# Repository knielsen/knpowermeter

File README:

Tiva TM4C version of blipduino.

Read blips on a powermeter with a photo-diode.
Use ADC comparator to detect blips.
Send data to master node using nRF24L01+.

Licence: GPL v2+.

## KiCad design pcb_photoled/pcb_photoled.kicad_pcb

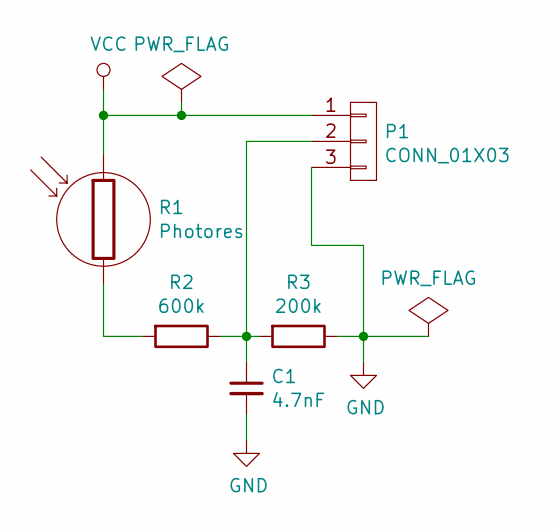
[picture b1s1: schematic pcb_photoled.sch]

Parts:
C1: 4.7nF; C_0805_HandSoldering
P1: CONN_01X03; Socket_Strip_Straight_1x03
R1: Photores; VBPW34
R2: 600k; R_0805_HandSoldering
R3: 200k; R_0805_HandSoldering

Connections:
GND: C1.2, P1.3, R3.1
unnamed: C1.1, P1.2, R2.1, R3.2
unnamed: R1.2, R2.2
VCC: P1.1, R1.1

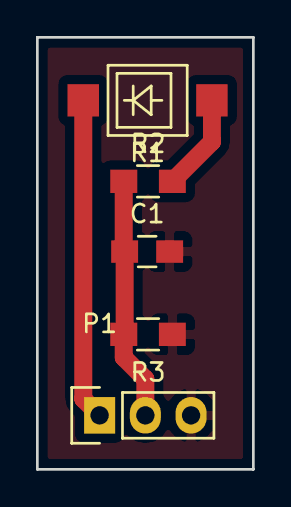
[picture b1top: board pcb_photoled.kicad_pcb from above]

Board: 2 copper layers, 12.0 x 24.0 mm, 5 parts (0 on the bottom side), 4 nets.

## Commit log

2015-12-28 Initial revision of photodiode breakout
2015-12-28 Initial commit for power_reader.
    Not complete, just a skeleton that compiles.
2016-01-01 Simple ADC test
2016-01-02 Implement comparator that triggers on voltage going high.
    Uses the hysteresis-once mode, to effectively implement
    schmitt-triggering. With a capacitor on the input, it seems to pretty
    reliably trigger only once on the high transision. Will need tuning
    (wrt. high/low levels and capacitor value) for the real hardware,
    though.
2016-01-02 Add a capacitor on the adc line, to suppress noise.
2016-01-02 Implement systick-based millisecond counter.
2016-01-02 Implement ADC comparator interrupt that computes blip milliseconds time
2016-01-03 Adjust to work with real blip hardware.
    Some code to measure min/max/avg/current voltage on the input signal, used
    to find the right low/high region for the ADC comparator hysteresis.
    Works fine to get blips from the power meter.
2016-01-03 Use a SMD footprint for the BPW photodiode.
    This revision was etched and used as v1 PCB for the knpowermeter.
2016-01-03 #ifdef out debug output by default.
2016-01-03 First revision of PCB etched.
2016-01-04 Implement sending blips over nRF.
    Should handle timeout and missing ack from receiver.
    Not fully tested yet (need implementation of receiver for that).
2016-01-04 Use the IRQ line when waiting for nRF24L01+ to complete sending
2016-01-04 Intermediate commit: some incomplete code for powermaster
2016-01-04 Fix usb for TM4C1232 MCU (without OTG).
2016-01-04 Flash the on-board LED for each blip.
2016-01-04 First working powermaster.
    Read blips from the nRF24L01+, and send them out over a simulated
    virtual COM port.
